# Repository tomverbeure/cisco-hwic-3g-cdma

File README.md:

# Cisco HWIC-3G-CDMA

There is a pretty detailed reverse-engineering write-up [here](https://tomverbeure.github.io/2019/11/11/Cisco-HWIC-3G-CDMA.html).

* Mentioned on [FPGA Board Hack](https://hackaday.io/project/159853-fpga-board-hack)
* [Product Datasheet](https://manualsbrain.com/en/manuals/18492/pdf/90717e773cac1934092aa5e5747f7dc69d763a4f12ae95196a2226f8e41b79ac/cisco-hwic-3g-hspa-g-hwic-3g-hspa-g-data-sheet.pdf)

# Components

Main Components:

* Altera Cyclone II EP2C35F484C8 FPGA

    * [Cyclone II Handbook Vol 1](https://www.intel.com/content/dam/www/programmable/us/en/pdfs/literature/hb/cyc2/cyc2_cii5v1.pdf)

* Micron MT46V16M16-6T 4 Meg x 4 banks x 16 (32MB total) Automotive DDR SDRAM (2.5V, 133MHz/167MHz)

    * [Datasheet](https://www.micron.com/-/media/client/global/documents/products/data-sheet/dram/mobile-dram/low-power-dram/lpddr/256mb_x8x16_at_ddr_t66a.pdf)

* NXP ISP1564HL HS USB PCI Host Controller

    * [Datasheet](https://www.alldatasheet.com/datasheet-pdf/pdf/255353/NXP/ISP1564HL.html)
    * 3.3V power supply.
    * Built-in 1.8V regulator.

* Sierra Wireless MC5727 Wireless Module

    * [Development Manuals](https://www.manualslib.com/products/Sierra-Wireless-Airprime-Mc5727-8797020.html)
    * Controlled by host over USB
    * Can be replaced by "Mini PCI-E to USB3.0 PCI Express Adapter Card PCI-E to USB 3.0 Expansion Card", a break-out
      board connects the mini card USB to a regular USB connector.

* JTAG connector follows ALTERA USB Blaster pinout`

Various Other Components:

* ADM3222 - Analog Devices Low Power 3.3V RS-232 Line Drivers/Receivers

    * [Datasheet](https://www.analog.com/media/en/technical-documentation/data-sheets/ADM3202_3222_1385.pdf)

* AT90SC12836RCT/C9059 Crypto Chip
* Maxim MXQ3311
    * 5V/3.3V level shifters?
* Ti CU257C - SN74CBT3257C - 4-bit multiplexer/demultiplexer 5V bus switch
    * ?

Power Regulators:

* Micrel MIC49150-1.2 LDO Regulator with dual input voltages
    * [Datasheet](http://ww1.microchip.com/downloads/en/DeviceDoc/mic49150.pdf) Located between FPGA and ISP1564HL
* MIC39102 Low Voltage Regulator
    * [Datasheet](http://ww1.microchip.com/downloads/en/DeviceDoc/20005834A.pdf)
* MIC37302 Low Voltage uCap LDO Regulator (3A)
    * [Datasheet](http://ww1.microchip.com/downloads/en/DeviceDoc/MIC37300-01-02-03-3.0A-Low-Voltage-microCap-LDO-Regulator-DS20006169A.pdf)
    * EN (pin 1) is controlled by FPGA (AB17)
    * 5V input
    * 3.3V output: goes to PCI Express Mini card.

Unpopulated:

* NOR Flash

    * [Datasheet](https://www.alldatasheet.com/datasheet-pdf/pdf/211036/SPANSION/S29GL032N90TFI040.html)

# Power

All essential componets for LED blinky are connected to 3.3V. No need for 5V power rail to make that work.

12V power connector of HWIC connector is not used.

# PC Express Mini Card Info

* PC Express Mini Card: 1x PCIe + USB 2.0
    * https://en.wikipedia.org/wiki/PCI_Express#PCI_Express_Mini_Card
    * 1.5V and 3.3V.
    * 1.5V not connected? MC5727 doesn't seem to need it.

# FPGA Bitstream Configuration

There are 3 ways to program a new bitstream into the FPGA:

* JTAG

    The most obvious way is to populate connector J10 with a 10-pin 5x2 connector, use a USB Blaster
    compatible JTAG dongle, and download new bitstreams with Quartus Programmer. This will be the default mode
    during RTL development.

    The holes of connector J10 are usually soldered shut on this board. The best way to add a JTAG connector
    is to solder it solidly in the place where it was intended to be. To do that, you'll first have to open
    up these 10 soldering holes. Desoldering needles are perfect for that. They only cost a few dollars on
    AliExpress, and it requires very little practice to learn how to use them.

    There are dirt cheap USB (~$2) Blaster clones out there, but these are based on a PIC or STM microcontroller.
    These very often don't work! You can read about this [here](https://tomverbeure.github.io/2018/04/18/Terasic-vs-Cheap-Clone-USB-Blaster.html).

    What you need is a USB Blaster that contains an FTDI chip and a CPLD, just like the real one from Intel. 
    One way to make sure you get that is to simply buy an official Intel one ($200!!!), or an 'official' clone 
    from Terasic (~$50). Or you buy a clone on AliExpress that explicty mentions "FT245+CPLD", like this: 

    Including shipping, you can find these for less than $15, and they behave exactly like the official ones.

    When not in development mode, you *could* also download a new bitstream through JTAG by using a so-called .jam 
    file (which contains all the JTAG transactions) and a Jam file player that runs on a small microcontroller.
    This solution has not been tried on this board, but there's no reason why it wouldn't work.
    Check out [Intel's documentation](https://www.intel.com/content/www/us/en/programmable/support/support-resources/support-centers/devices/programming-tools/jam-stapl/tls-jam-embedded.html) 
    on this.

* Passive Serial

    This is the way this Cisco has been configured: an external CPU (in this case, the Cisco router that hosts
    this board), sends the bitstream to the PCB.

    Alternatively, just like with the JTAG .jam player, one could make this work with a small external
    microcontroller.

    <To be implemented>

* Active Serial

    Most FPGA board use this mode. It requires an on-board serial PROM that contains the bitstream. At
    powerup, the FPGA autonomously loads the bitstream from the PROM. No other active component are required.
    The Cisco board doesn't use this because it will always be used inside a router that has the capability to
    upload the bitstream in passive serial mode. And thus, there's no serial PROM on the board either.

    However, it is possible to retrofit the board with a serial PROM.

    It's obvious that this requires some soldering skills, and even then it's a pretty fragile solution.
    But it does work!

##  Active Serial Retrofit

Steps:

* Change MSEL[1:0] setting on FPGA from 2'b01 (passive serial mode) to 2'b10 (active serial)

   Remove resistor R60. This is a pullup resistor that pulls MSEL[0] to VCCIO. The FPGA has
   built-in pulldown resistors, so there is no need to add that. (It's interesting that resistor
   R59 is a pulldown resistor for MSEL[1], which is redudant...) 

* Remove SOT3-5 device that drives DCLK.

    In passive mode, DCLK is an FPGA input, now it becomes an FPGA output.

* Glue serial PROM onto the board in dead-bug position

    The best location is empty space for the unpopulated NOR flash.

    Make sure you install a 64Mbit PROM: an 8Mbit PROM is sufficient for this FPGA, but Quartus only 
    supports EPCS4 or EPC64 devices. If you mistakenly installed an 8Mbit PROM, chances are that you
    can still make it work by preparing a .jic file for a 4Mbit EPCS4 and enabling bitstream
    compression, which should reduce the bitstream size from the required 6Mbit to below 4Mbit.

* Wire up all the serial PROM pins

    Need to 

    <FIXME: comprehensive list and pictures of convenient place to tap the required signals.>

# Examples

* [Blinky](./blinky)

    The Hello World of FPGAs!

* [RS-232](./rs232)

    RS232 loopback: what gets send to UART_RXD is sent back to UART_TXD.

# FPGA Pin Connections

The pin location declaration for Quartus can be found in [./pinout.tcl](./pinout.tcl). Example projects
won't necessarily use this file, e.g. if some IP uses a different name.

FPGA Pins:

```
CLK25                   : L2
LED_GREEN_CR1           : AA19
LED_GREEN_CR3           : AB19
LED_GREEN_CR5           : AA15
LED_ORANGE_CR5          : AB15

UART_DRV_ENA_           : N6 (ADM3222/EN_) - Receiver Enable. Must be 0 to enable RX.
UART_DRV_SD_            : P6 (ADM3222/SD_) - Shutdown Control. Must be 1 to enable TX.
UART_TXD                : D6 (ADM3222/T1IN)
UART_RXD                : F4 (ADM3222/R1IN)
UART_RTS                : G6 (ADM3222/T2IN)
UART_CTS                : H6 (ADM3222/R2IN)

MSEL0                   : M17   - Pulled high with R60
MSEL1                   : N17   - Pulled low with R63
```

HWIC Pins:

23 GPIOs from FPGA on HWIC connector:

```
        1	-	    -	        35
		2	GND	    GND	        36
	70	3	G21	    GND	        37          3 == toggling output on Cisco router
		4	GND	    *  	        38
	71	5	-       GND	        39
		6	GND	    -	        40
	72	7	-	    -	        41
		8	-	    -	        42
	73	9	-	    -	        43
		10	GND	    GND	        44
	74	11	G22	    F21	        45          11 = DATA0
		12	E21	    E22	        46
	75	13	D21     D22	        47
		14	C21     C22	        48
	76	15	J22     *  	        49          49 == MXQ12 and nCONFIG_OE_
		16	*  	    N22	        50          16 == nCONFIG and MXQ12_OE_
	77	17	-	    GND	        51
		18	T22	    U21	        52
	78	19	V21	    V22	        53
		20	W21	    W22	        54
GND	79	21	Y21	    Y22	        55
		22	3.3V    N21	        56
5.0	80	23	MXQ1    -	        57
		24	GND	    MXQ2        58
GND	81	25	T21	    -	        59          25 == DCLK_OE_ / 59 == DCLK, pulled high to 3.3V
		26	*  	    *  	        60
3.3	82	27	*  	    *  	        61
		28	*  	    -           62
GND	83	29	GND	    *  	        63
		30	*  	    GND	        64
12.	84	31	GND	    *  	        65
		32	A12	    GND	        66          32: FPGA input only. Goes to clock input.
	    33	GND	    L18/MXQ7    67
		34	-   	-	        68
```

SOT23-5 ICs:

* U3: 'VE': AND gate
* U7: 'AN': 74AHC1G126: Tri-state buffer with active high OE
* U9: 'CGK' or 'VG': SN74LVC1G32: OR gate

AT90SC12836RCT/C9059 connections:
```
1:      GND                         8:      5V
2:      -                           7:      Pin 13 of MXQ3311
3:      Pin 6 and 9 of MXQ3311      6:      -
4:      Pin 11 of MXQ3311           5:      Pin 8  of MXQ3311
```

AT90SC12836RCT/C9059 connections on VWIC-2MFT-T1/E1 board:
```
1:      GND                     8:      5V
2:      -                       7:      Pin 13 of MXQ3311
3:      Pin 9  of MXQ3311       6:      -
4:      Pin 11 of MXQ3311       5:      Pin 8  of MXQ3311
```

MXQ3311 connections:
```
1:      Pin 23 of HWIC         14:
2:      Pin 58 of HWIC         13: Pin 7 of C9059
3:                             12:
4:      GND                    11: Pin 4 of C9059
5:                             10: 3.3V
6:      Pin 3 of C9059          9: Pin 3 of C9059
7:      Pin 67 of HWIC/L18      8: Pin 5 of C9059
```

SDRAM to FPGA connections:
```
DQ0         : B20

DQ1         : A20
DQ2         : B19

DQ3         : A19
DQ4         : D16

DQ5         : E15
DQ6         : D15

DQ7         : C14

LDQS        : A17

LDM         : E14
WE_         : B14
CAS_        : B17
RAS_        : B18
CS_         : A5

BA0         : C17
BA1         : C18
A10/AP      : A3
A0          : A10
A1          : A9
A2          : A7
A3          : B11

DQ15        : F12

DQ14        : A15
DQ13        : B15

DQ12        : A16
DQ11        : B16

DQ10        : F13
DQ9         : F14

DQ8         : D14

UDQS        : A13

UDM         : A14

CK#         : B4
CK          : A4
CKE         : C9

A12         : D9
A11         : D11
A9          : B5
A8          : B6
A7          : B7
A6          : B8
A5          : B9
A4          : B10
```

Empty TSOP-48 (NOR flash?) footprint to FPGA:
```
pin  1 : AA17           Pin 48:  Y17
pin  2 :  W16           Pin 47: Pin 14      pulled high.
pin  3 :  V15           Pin 46: GND
pin  4 :  W15           Pin 45:  AB10
pin  5 :  V14           Pin 44:  AB8
pin  6 :  W14           Pin 43:   V9
pin  7 :  Y14           Pin 42:   W7
pin  8 : AA14           Pin 41:   W9
pin  9 :  U10           Pin 40:  AA7
pin 10 :  U13           Pin 39:  AA9
pin 11 :  Y20           Pin 38:  AB7
pin 12 :  Y13           Pin 37: VCCIO
pin 13 : NC             Pin 36:  AB9
pin 14 : Pin 47         Pin 35:   Y5
pin 15 : ???            Pin 34:   V8
pin 16 :  U9            Pin 33:   Y6
pin 17 :  U8            Pin 32:   W8
pin 18 : AB14           Pin 31:  AA6
pin 19 : AA13           Pin 30:  AA8
pin 20 : AB13           Pin 29:  AB6
pin 21 : AA12           Pin 28:  Y19
pin 22 :  V11           Pin 27: GND
pin 23 :  W11           Pin 26:  Y18
pin 24 : AA11           Pin 25: AA10
```
Important: there's at least one connection wrong in the table above. Need to revisit...

PCI USB Host to FPGA:
```
Pin  4: INTA_           :   AA5
Pin  5: RST_            :   AB18
Pin  6: SYS_TUNE        :               "Always connect to ground."
Pin  7: CLK             :   E19
Pin  8: GNT_            :   J1
Pin  9: REQ_            :   AB4
Pin 10: AD[31]          :   C1
Pin 11:
Pin 12: AD[30]          :   D2
Pin 13: AD[29]          :   D1
Pin 14: AD[28]          :   E1
Pin 15: AD[27]          :   D4
Pin 16:
Pin 17:
Pin 18:
Pin 19:
Pin 20: AD[26]          :   E4
Pin 21: AD[25]          :   E3
Pin 22: AD[24]          :   E2
Pin 23: CBE_[3]         :   Y4
Pin 24: IDSEL           :   E2          Same as AD[24]
Pin 25:

Pin 26: AD[23]          :   F3
Pin 27: AD[22]          :   F2
Pin 28: AD[21]          :   F1
Pin 29: AD[20]          :   G5
Pin 30: AD[19]          :   G3
Pin 31: AD[18]          :   H4
Pin 32:
Pin 33: AD[17]          :   H2
Pin 34: AD[16]          :   H1
Pin 35: CBE_[2]         :   Y3
Pin 36: FRAME_          :   W1
Pin 37: IRDY_           :   W2
Pin 38: TRDY_           :   W3
Pin 39: DEVSEL_         :   W4
Pin 40:
Pin 41: STOP_           :   V1
Pin 42: CLKRUN_         :               10K resistor to GNDA (pin 61)
Pin 43:
Pin 44: PERR_           :   V2
Pin 45: SERR_           :   V4
Pin 46:
Pin 47: PAR             :   U2
Pin 48: CBE_[1]         :   Y2
Pin 49:
Pin 50: AD[15]          :   J4

Pin 51: AD[14]          :   J2
Pin 52: AD[13]          :   N4
Pin 53: AD[12]          :   N3
Pin 54: AD[11]          :   N2
Pin 55:
Pin 56: AD[10]          :   N1
Pin 57: AD[9]           :   P5
Pin 58:
Pin 59: AD[8]           :   P2
Pin 60: CBE_[0]         :   Y1
Pin 61:
Pin 62: AD[7]           :   P1
Pin 63: AD[6]           :   R5
Pin 64:
Pin 65: AD[5]           :   R2
Pin 66: AD[4]           :   R1
Pin 67: AD[3]           :   T5
Pin 68: AD[2]           :   U3          Uncertain. Might be swapped with AD[3] or AD[1].
Pin 69: AD[1]           :   T3
Pin 70: AD[0]           :   T2
Pin 71:
Pin 72:
Pin 73:
Pin 74: XTAL2           :               Pulled down to GND
Pin 75: XTAL1           :               Going to FPGA with resistive divider?

Pin 76:
Pin 77:
Pin 78: OC1_N           :               Connected to OC2_N. Pulled up to VCCIO.
Pin 79: PWE1_N          :
Pin 80:
Pin 81: RREF            :
Pin 82:
Pin 83: DM1             :
Pin 84:
Pin 85: DP1             :
Pin 86:
Pin 87: OC2_N           :
Pin 88: PWE2_N          :
Pin 89:
Pin 90: DM2             :
Pin 91:
Pin 92: DP2             :
Pin 93:
Pin 94:
Pin 95:
Pin 96: SCL             :               Used for config EEPROM. Not used on this board.
Pin 97: SDA             :
Pin 98:
Pin 99: PME_            :               ?
Pin 100:
```

Miscellanous Pins:
```
AB17                    : pin 1 (EN) of MIC37302
```

# NOR Flash

The PCB has an unpopulated TSOP-48 footprint. The pads of this footprint match the requirements
for NOR flash.

*Some NAND flash also has a TSOP-48 footprint, but the pinout is not compatible. So NOR flash only.*

Pin 15 on this package is not routed to the FPGA, but its function is `RY/BY#`, the status of program or erase operation.
There are other ways for the FPGA to figure out this status, so it's not strictly needed.

Pin 47 (`BYTE#$`) is often used in these flash devices to select between 8-bit or 16-bit mode. On the
PCB, it is connected to pin 14 `wp#`). On a live board, these pins have a level of 3.3V, which is
good, because otherwise the flash would be write protected. There is an unpopulated resistor on these
pins that is connected to ground. There is no reason to populated this pin.

NOR flash:

* 256K x16 (e.g. Microchip SST39VF401C)

    * Matches. Pins 9, 10, 16 are NC on this chip.
    * Pin 47 is NC. (So no selection between 8bit or 16bit mode.

* 1M x 8bit or 256K x16 (e.g. Cypress S29AL008J)

    * Matches. Pins 9, 10, 16 are NC on this chip.
    * Pin 47 (BYTE#) selects between 8bit or 16bit mode. 3.3V -> 16bit mode only.

* 4M x8 or 2M x16 (e.g. Cypress S29J032J)

    * Matches.
    * Pin 47 (BYTE#) selects between 8bit or 16bit mode. 3.3V -> 16bit mode only.

* 8M x8 or 4M x16 (e.g. Cypress S29GL064S)

    * No Match!
    * Some models require pin 13 for bit A21, others requires pin 15 for A19. Both pin 13 and pin 15
      aren't connected to the FPGA.

Conclusion: it's possible to solder a NOR flash onto this PCB with a maximum size of 32Mbit. When
both 8bit and 16bit more are supported, the flash should be used in 16-bit mode. The pulldown
resistor should not be populated.

# Other Cisco boards with an FPGA:

* Cisco VWIC3-1MFT-T1/E1 ($4!)

    * Contains an Altera Stratix II EP2S15 (supported by Quartus Web Edition)

* Cisco VWIC3-2MFT-T1/E1 ($5!)

    * Contains an Altera Stratix II EP2S30 (NOT supported by Quartus Web Edition)
    * See https://github.com/tomverbeure/cisco-vwic3-2mft
    * See https://hackaday.io/project/159853-fpga-board-hack/log/161719-stratix-ii-cisco-vwic3-2mft)

* Cisco VWIC-2MFT-T1-DI

    * Xilinx FPGA Spartan XCS30 PQ208CKN9931

        Super old: 1368 logic cells / 1536 FFs
        https://www.ece.iastate.edu/~zambreno/classes/cpre583/documents/xilinx/ds060.pdf

    * MC68LC302 microcontroller
    * 64Kx16 SRAM
    * T1/E1 framers

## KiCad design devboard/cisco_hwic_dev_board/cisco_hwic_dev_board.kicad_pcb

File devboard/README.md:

# Breakout board

**IMPORTANT: DO NOT USE THE CURRENT PCB. IT'S COMPLETELY BROKEN!!!**

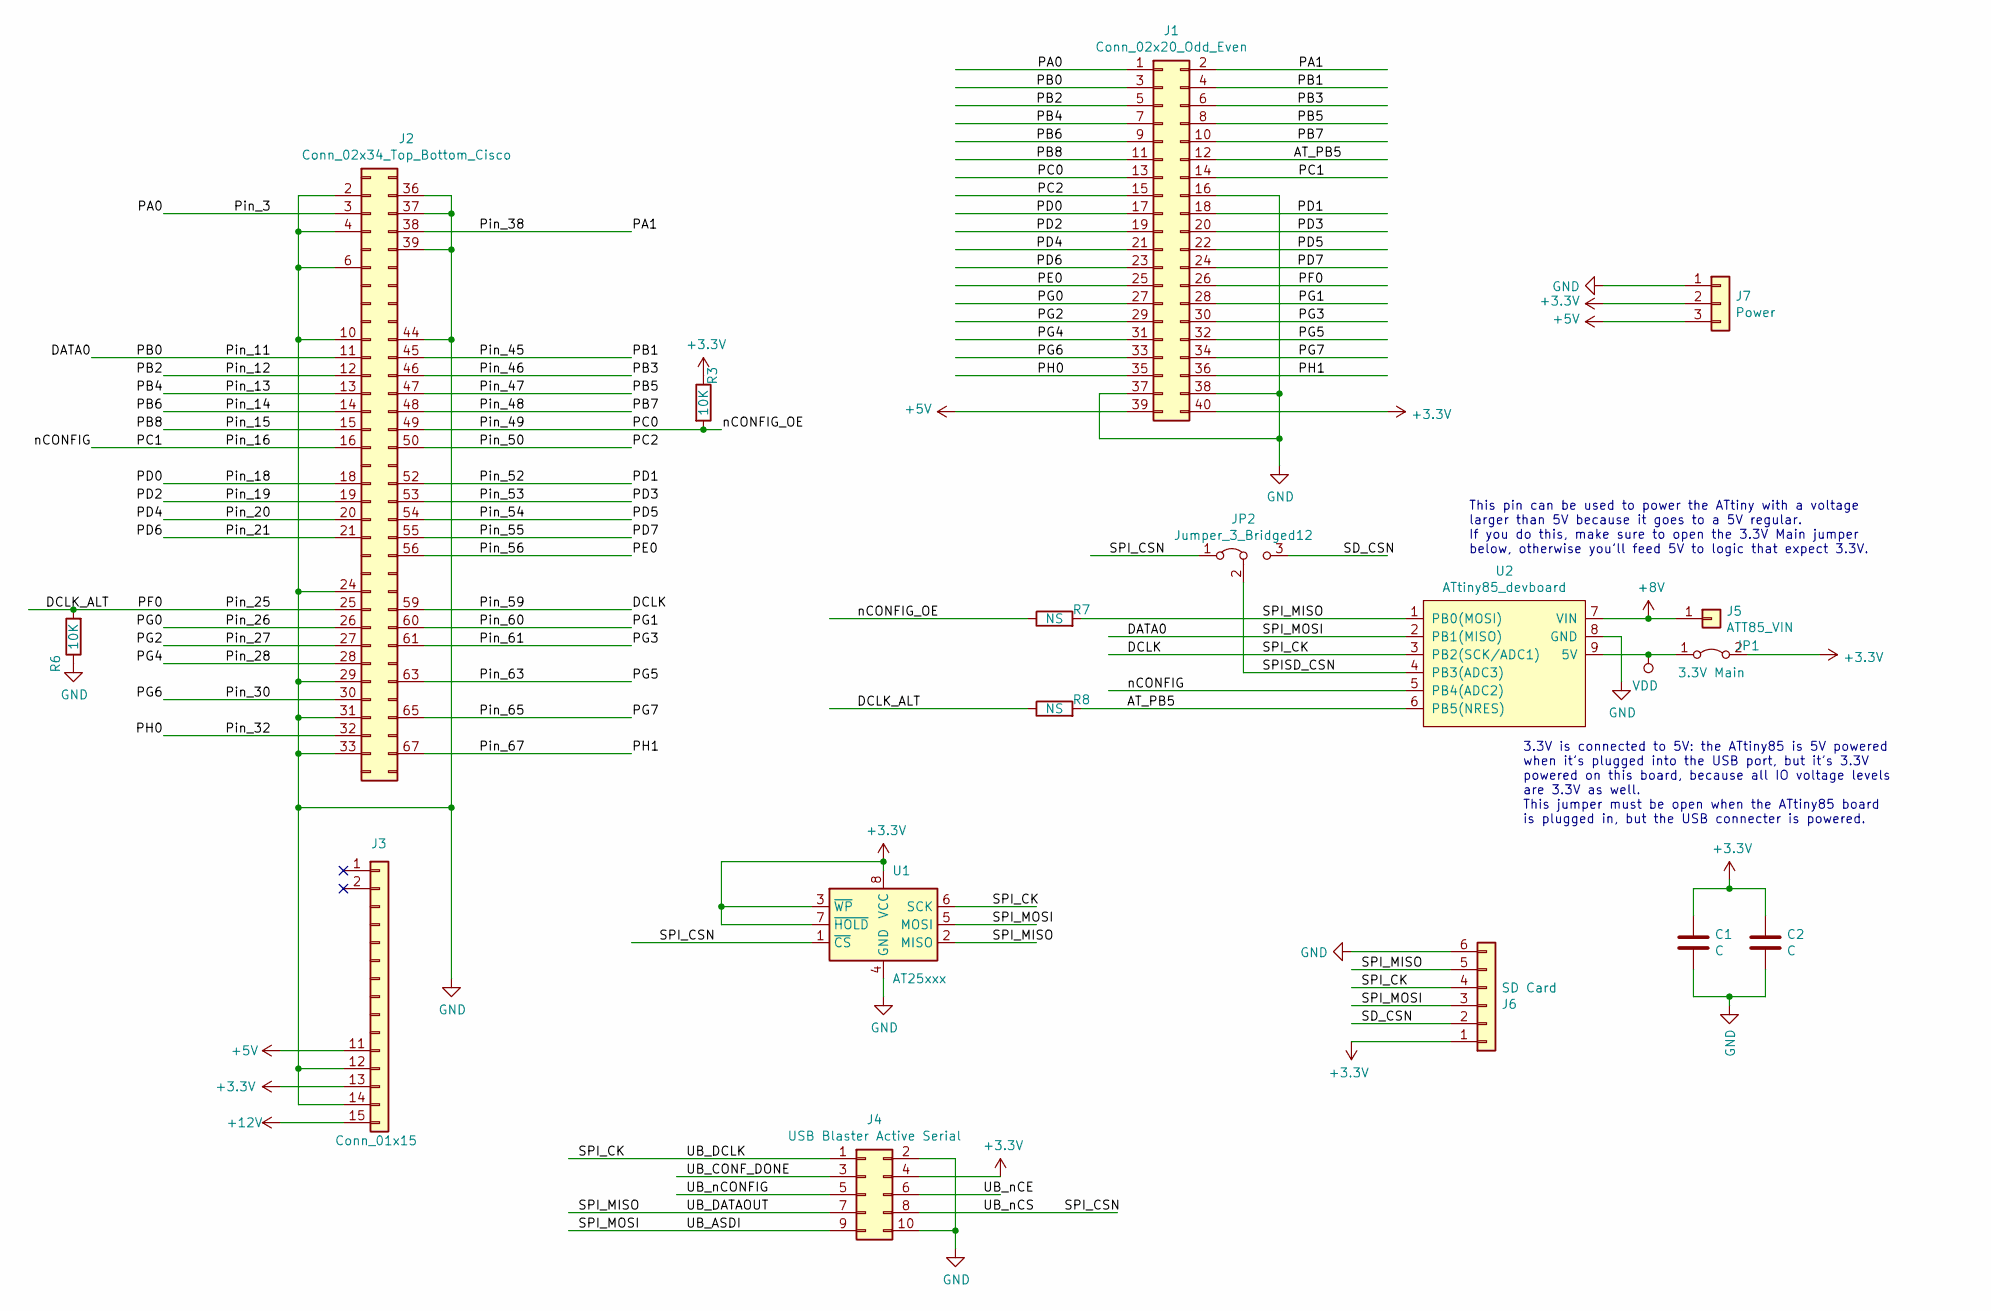
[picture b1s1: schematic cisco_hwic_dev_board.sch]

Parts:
C1, C2: C; C_0603_1608Metric_Pad1.05x0.95mm_HandSolder
J1: Conn_02x20_Odd_Even; PinHeader_2x20_P2.54mm_Vertical
J2: Conn_02x34_Top_Bottom_Cisco; PinHeader_2x34_P1.27mm_Vertical_Top_Bottom
J3: Conn_01x15; PinHeader_1x15_P2.54mm_Vertical_Cisco
J4: USB Blaster Active Serial; PinHeader_2x05_P2.54mm_Vertical
J5: ATT85_VIN; PinHeader_1x01_P2.54mm_Vertical
J6: SD Card; PinHeader_1x06_P2.54mm_Vertical
J7: Power; PinHeader_1x03_P2.54mm_Horizontal
JP1: 3.3V Main; PinHeader_2x01_P2.54mm_Vertical
JP2: Jumper_3_Bridged12; PinHeader_1x03_P2.54mm_Vertical
R3, R6: 10K; R_0603_1608Metric_Pad1.05x0.95mm_HandSolder
R7, R8: NS; R_0603_1608Metric_Pad1.05x0.95mm_HandSolder
U1: AT25xxx; SOIC-8_5.275x5.275mm_P1.27mm
U2: ATtiny85_devboard; Digispark_ATtiny85

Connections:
+3V3: C1.1, C2.1, J1.40, J3.13, J4.4, J6.1, J7.2, JP1.2 (B), R3.1, U1.3 (~WP), U1.7 (~HOLD), U1.8 (VCC)
+5V: J1.39, J3.11, J7.3
+8V: J5.1, U2.7 (VIN)
+12V: J3.15
/AT_PB5: J1.12, R8.2, U2.6 (PB5(NRES))
/DATA0: J1.3, J2.11, J4.9, J6.3, U1.5 (MOSI), U2.2 (PB1(MISO))
/DCLK: J2.59, J4.1, J6.4, U1.6 (SCK), U2.3 (PB2(SCK/ADC1))
/DCLK_ALT: J1.26, J2.25, R6.2, R8.1
/PA0: J1.1, J2.3
/PA1: J1.2, J2.38
/PB1: J1.4, J2.45
/PB2: J1.5, J2.12
/PB3: J1.6, J2.46
/PB4: J1.7, J2.13
/PB5: J1.8, J2.47
/PB6: J1.9, J2.14
/PB7: J1.10, J2.48
/PB8: J1.11, J2.15
/PC0: J1.13, J2.49, R3.2, R7.1
/PC1: J1.14, J2.16, U2.5 (PB4(ADC2))
/PC2: J1.15, J2.50
/PD0: J1.17, J2.18
/PD1: J1.18, J2.52
/PD2: J1.19, J2.19
/PD3: J1.20, J2.53
/PD4: J1.21, J2.20
/PD5: J1.22, J2.54
/PD6: J1.23, J2.21
/PD7: J1.24, J2.55
/PE0: J1.25, J2.56
/PG0: J1.27, J2.26
/PG1: J1.28, J2.60
/PG2: J1.29, J2.27
/PG3: J1.30, J2.61
/PG4: J1.31, J2.28
/PG5: J1.32, J2.63
/PG6: J1.33, J2.30
/PG7: J1.34, J2.65
/PH0: J1.35, J2.32
/PH1: J1.36, J2.67
/SD_CSN: J6.2, JP2.3 (B)
/SPISD_CSN: JP2.2 (C), U2.4 (PB3(ADC3))
/SPI_CSN: J4.8, JP2.1 (A), U1.1 (~CS)
/SPI_MISO: J4.7, J6.5, R7.2, U1.2 (MISO), U2.1 (PB0(MOSI))
/UB_CONF_DONE: J4.3
/UB_nCE: J4.6
/UB_nCONFIG: J4.5
GND: C1.2, C2.2, J1.16, J1.37, J1.38, J2.2, J2.4, J2.6, J2.10, J2.24, J2.29, J2.31, J2.33, J2.36, J2.37, J2.39, J2.44, J3.12, J3.14, J4.2, J4.10, J6.6, J7.1, R6.1, U1.4 (GND), U2.8 (GND)
VDD: JP1.1 (A), U2.9 (5V)

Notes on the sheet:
3.3V is connected to 5V: the ATtiny85 is 5V powered when it’s plugged into the USB port, but it’s 3.3V powered on this board, because all IO voltage levels are 3.3V as well. This jumper must be open when the ATtiny85 board is plugged in, but the USB connecter is powered.
This pin can be used to power the ATtiny with a voltage larger than 5V because it goes to a 5V regular. If you do this, make sure to open the 3.3V Main jumper below, otherwise you’ll feed 5V to logic that expect 3.3V.

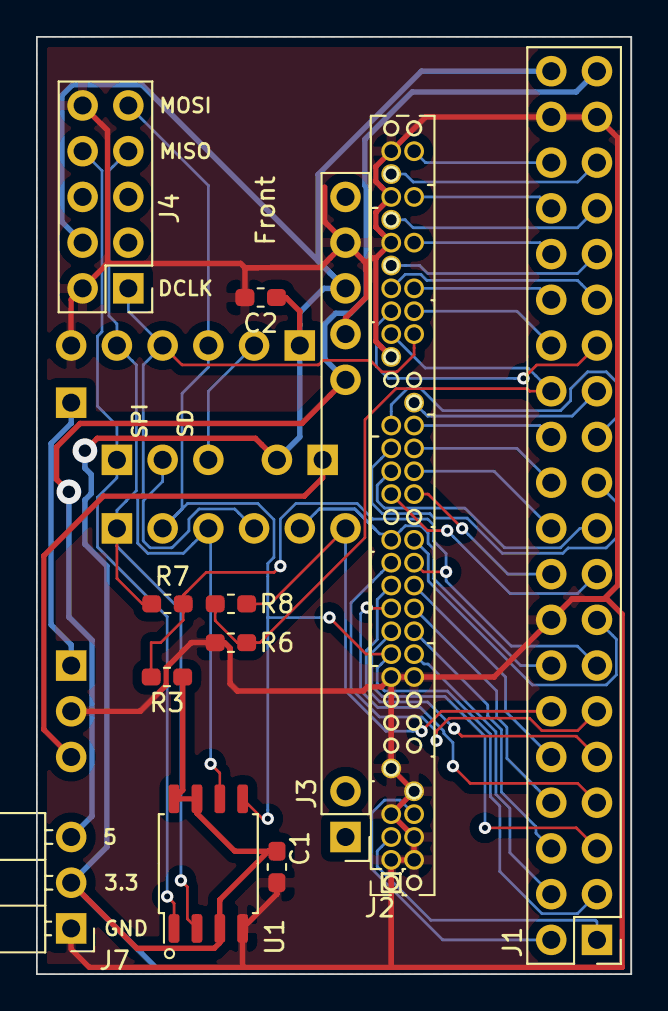
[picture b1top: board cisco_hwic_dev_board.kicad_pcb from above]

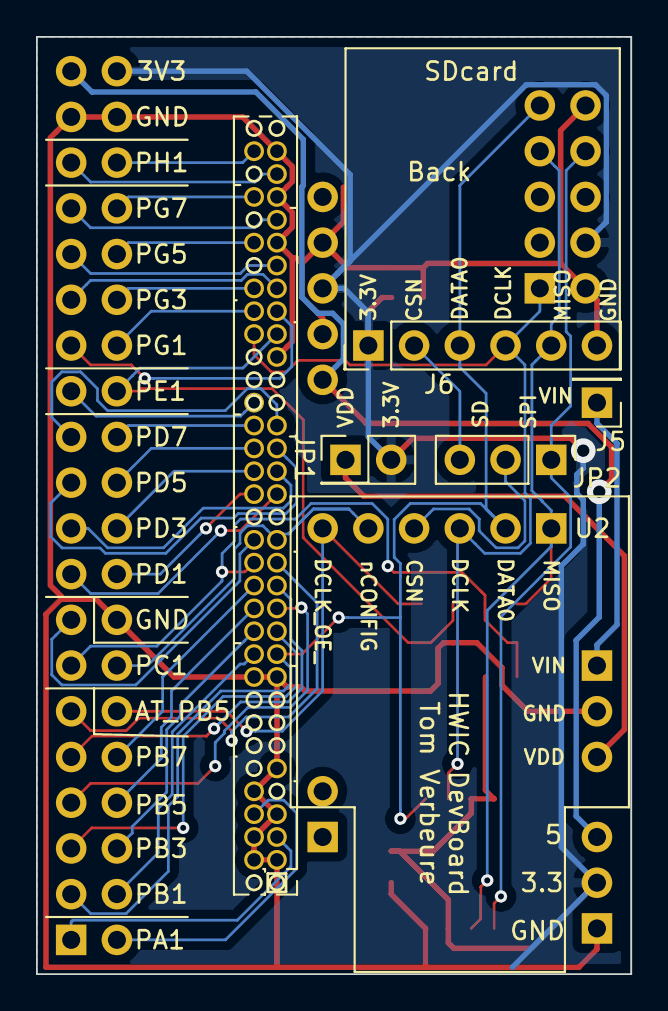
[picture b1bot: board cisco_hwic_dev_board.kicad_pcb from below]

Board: 2 copper layers, 33.0 x 52.1 mm, 17 parts (5 on the bottom side), 45 nets.

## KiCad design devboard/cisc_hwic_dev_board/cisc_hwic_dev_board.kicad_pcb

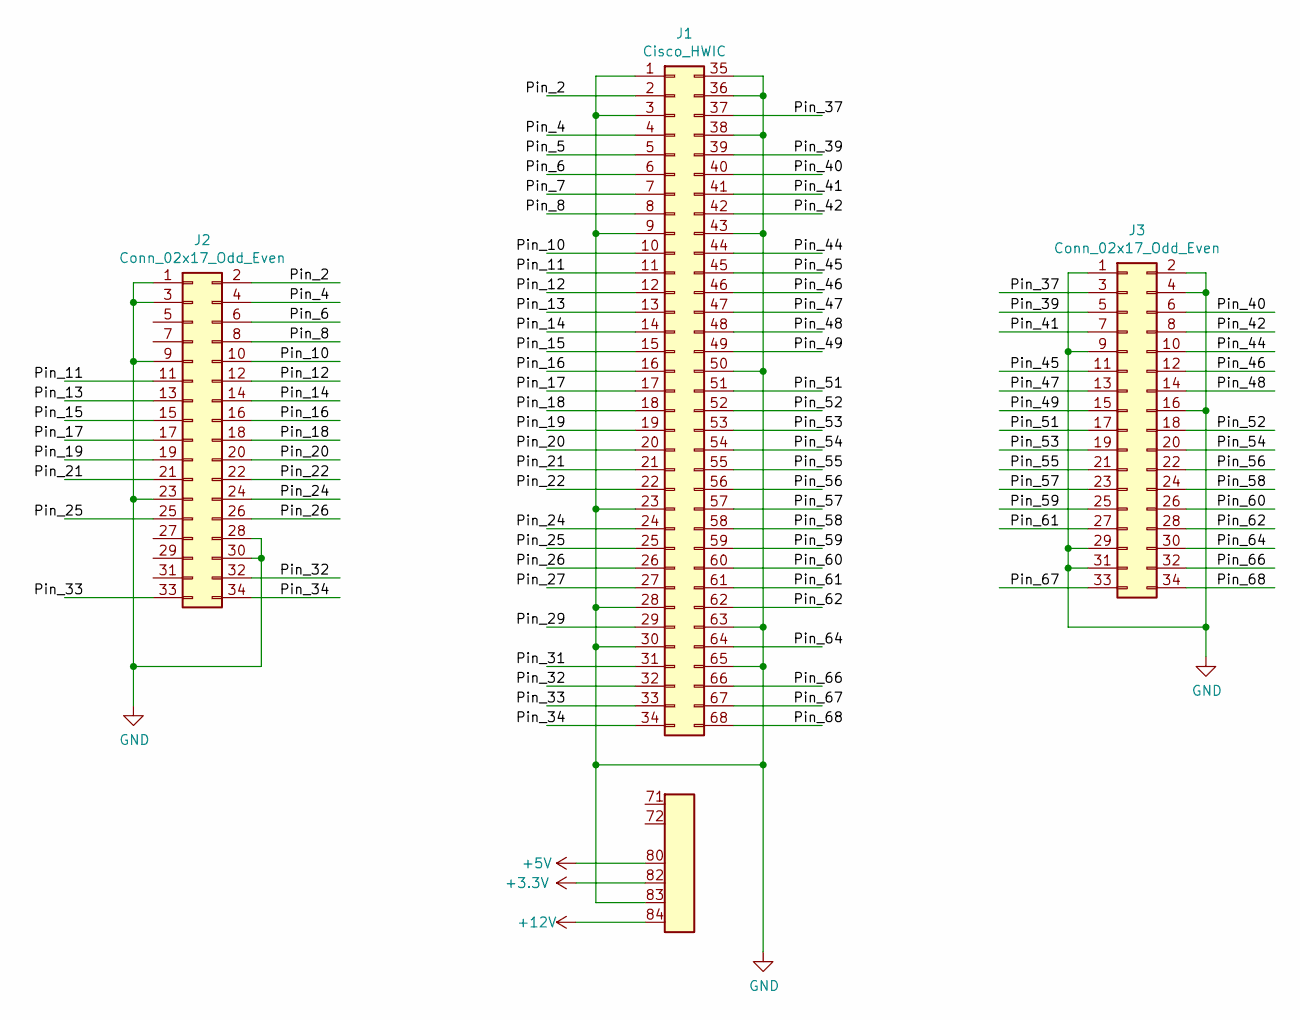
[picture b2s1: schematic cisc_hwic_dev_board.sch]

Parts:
J1: Cisco_HWIC; PinHeader_2x34_P1.27mm_Vertical_SMD_Top_Bottom
J2, J3: Conn_02x17_Odd_Even; PinHeader_2x17_P2.54mm_Vertical

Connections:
+3V3: J1.82 (3.3V)
+5V: J1.80 (5V)
+12V: J1.84 (12V)
/Pin_2: J1.2, J2.2
/Pin_4: J1.4, J2.4
/Pin_5: J1.5
/Pin_6: J1.6, J2.6
/Pin_7: J1.7
/Pin_8: J1.8, J2.8
/Pin_10: J1.10, J2.10
/Pin_11: J1.11, J2.11
/Pin_12: J1.12, J2.12
/Pin_13: J1.13, J2.13
/Pin_14: J1.14, J2.14
/Pin_15: J1.15, J2.15
/Pin_16: J1.16, J2.16
/Pin_17: J1.17, J2.17
/Pin_18: J1.18, J2.18
/Pin_19: J1.19, J2.19
/Pin_20: J1.20, J2.20
/Pin_21: J1.21, J2.21
/Pin_22: J1.22, J2.22
/Pin_24: J1.24, J2.24
/Pin_25: J1.25, J2.25
/Pin_26: J1.26, J2.26
/Pin_27: J1.27
/Pin_29: J1.29
/Pin_31: J1.31
/Pin_32: J1.32, J2.32
/Pin_33: J1.33, J2.33
/Pin_34: J1.34, J2.34
/Pin_37: J1.37, J3.3
/Pin_39: J1.39, J3.5
/Pin_40: J1.40, J3.6
/Pin_41: J1.41, J3.7
/Pin_42: J1.42, J3.8
/Pin_44: J1.44, J3.10
/Pin_45: J1.45, J3.11
/Pin_46: J1.46, J3.12
/Pin_47: J1.47, J3.13
/Pin_48: J1.48, J3.14
/Pin_49: J1.49, J3.15
/Pin_51: J1.51, J3.17
/Pin_52: J1.52, J3.18
/Pin_53: J1.53, J3.19
/Pin_54: J1.54, J3.20
/Pin_55: J1.55, J3.21
/Pin_56: J1.56, J3.22
/Pin_57: J1.57, J3.23
/Pin_58: J1.58, J3.24
/Pin_59: J1.59, J3.25
/Pin_60: J1.60, J3.26
/Pin_61: J1.61, J3.27
/Pin_62: J1.62, J3.28
/Pin_64: J1.64, J3.30
/Pin_66: J1.66, J3.32
/Pin_67: J1.67, J3.33
/Pin_68: J1.68, J3.34
GND: J1.1, J1.3, J1.9, J1.23, J1.28, J1.30, J1.35, J1.36, J1.38, J1.43, J1.50, J1.63, J1.65, J1.83, J2.1, J2.3, J2.9, J2.23, J2.28, J2.30, J3.1, J3.2, J3.4, J3.9, J3.16, J3.29, J3.31

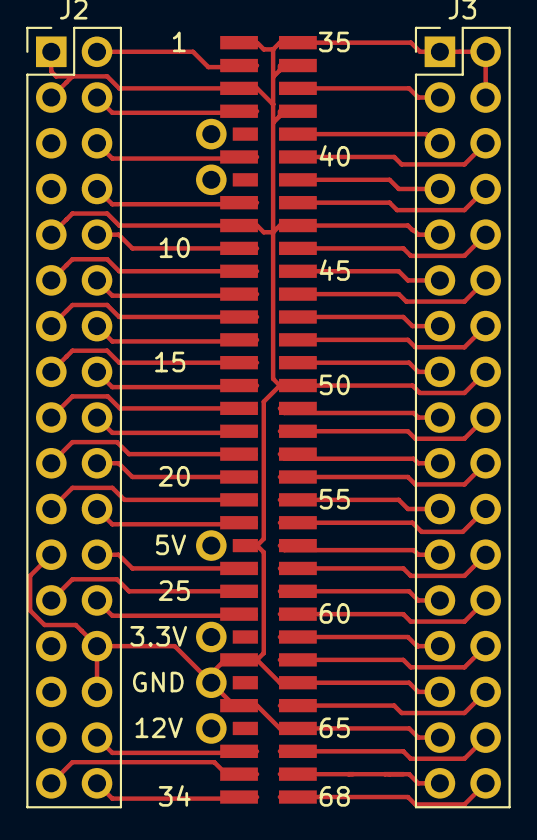
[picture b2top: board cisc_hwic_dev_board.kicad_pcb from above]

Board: 2 copper layers, 3 parts (0 on the bottom side), 51 nets.

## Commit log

2019-11-09 Initial commit.
2019-11-10 PCB front annotated.
2019-11-10 Blinky.
2019-11-13 Lots of new pins.
2019-11-13 SDRAM half-way done.
2019-11-15 All SDRAM pins identified.
2019-11-18 A bit of cleanup.
2019-11-18 Add link to blog post.
2019-11-19 Blinky example.
2019-11-19 Link to blinky.
2019-11-19 Add pinout.tcl.
2019-11-19 Pin comments.
2019-11-19 TABs.
2019-11-19 Set language to Verilog.
2019-11-19 Add pinout information of empty TSOP-48 footprint for NOR flash.
2019-11-20 Links to datasheets
2019-11-20 More datasheets.
2019-11-20 Copy blinky -> rs232
2019-11-20 Working RS232 loopback.
2019-11-20 Formatting.
2019-11-25 PCI to FPGA connections.
2019-11-25 Project to figure out all pin connections
2019-11-25 Fix some pin info.
    How did DDR pins get so wrong???
2019-11-25 pci_mini_33V_ena pin.
2019-11-25 BSCAN dump of board while inside router.
2019-11-25 Add FPGA BSCAN pin renamings.
2019-11-26 pci_xtal pin identified.
2019-11-26 Add hwic pins to pinout.
2019-11-26 MSEL resistors.
2019-11-27 Pics.
2019-11-30 USB Blaster.
2019-11-30 FPGA configuration.
2019-11-30 More info about configuration.
2019-12-01 Remove non-existent connector pins.
2019-12-01 Breakout board. WIP.
2019-12-01 Rename.
2019-12-02 More HWIC connector annotations.
2019-12-02 Expansion connector experiment.
2019-12-02 Expansion connector routed.
2019-12-08 Add ATtiny dev board.
2019-12-08 First version.
2019-12-15 README for dev board
2019-12-16 Various fixes after broken rev 1.
2019-12-17 Move ATtiny and SDcard for accessibility while soldered down.
2019-12-22 Read file from SD card. Seems to work.
2019-12-22 Add README.md with instructions.
2019-12-23 Fast version of SD card access. (Non-functional for now.)
2019-12-26 Bitstream init trace.
2019-12-27 Remove duplicate Pin_60.
2019-12-27 Remove 2 resistors. Connect AT_PB5.
2019-12-28 Add Cisco router commands.
2020-01-01 Change 2x34 connector footprint. Increase distance to HWIC connector.
2020-01-01 rev3 Gerbers.
2020-01-02 devboard rev2 comments.
2020-01-07 Latest version.
